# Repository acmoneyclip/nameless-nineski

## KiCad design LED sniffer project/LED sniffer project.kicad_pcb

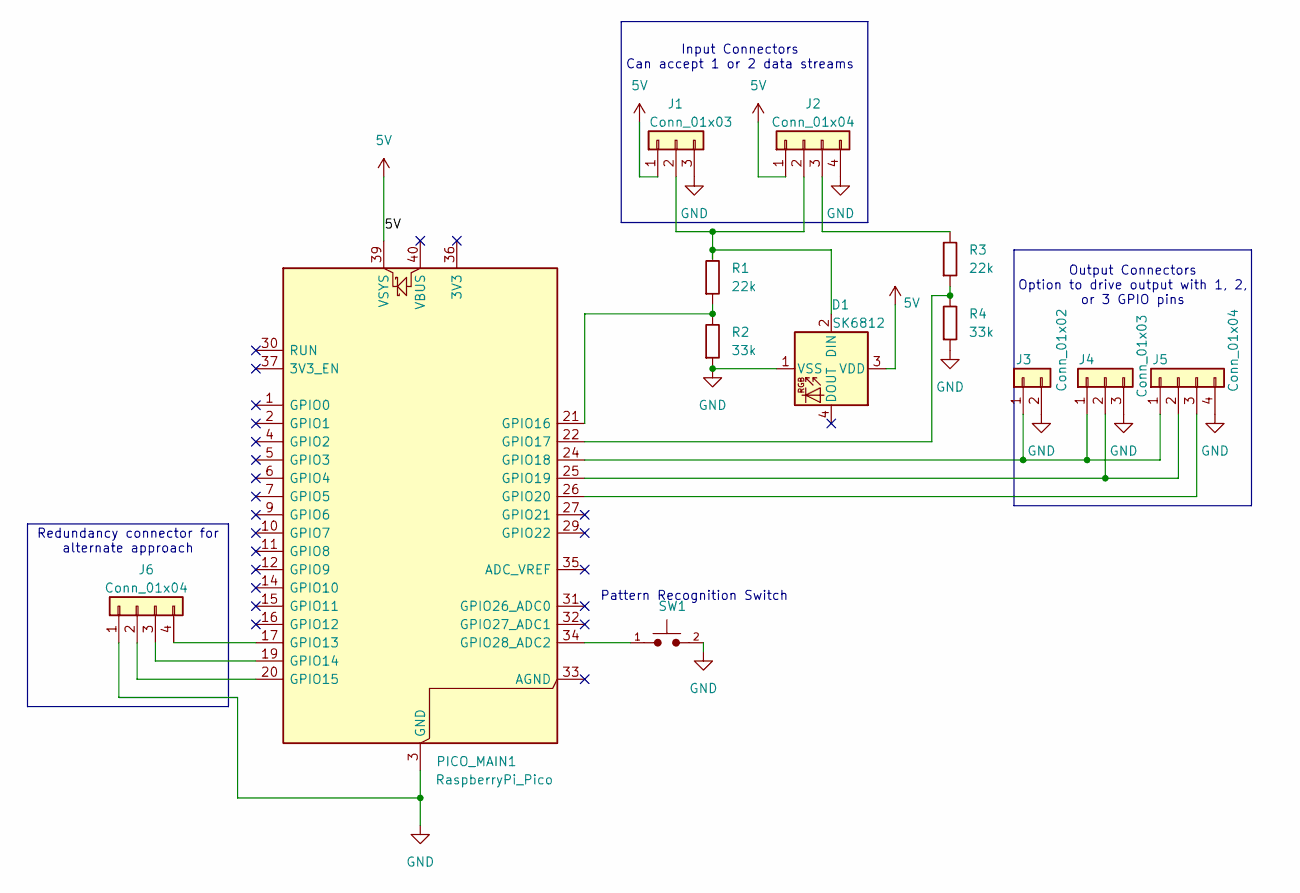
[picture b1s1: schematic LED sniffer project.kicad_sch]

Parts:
D1: SK6812; LED_SK6812_PLCC4_5.0x5.0mm_P3.2mm
J1, J4: Conn_01x03; PinHeader_1x03_P2.54mm_Vertical; Part Number 1-0301FBV0T
J2, J5, J6: Conn_01x04; PinHeader_1x04_P2.54mm_Vertical; Part Number 1-0401FBV0T
J3: Conn_01x02; PinHeader_1x02_P2.54mm_Vertical; Part Number 1-0201FBV0T
PICO_MAIN1: RaspberryPi_Pico; RaspberryPi_Pico_Common_Unspecified
R1, R3: 22k; R_0603_1608Metric
R2, R4: 33k; R_0603_1608Metric
SW1: Push_Button; SW_PUSH_6mm

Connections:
5V: D1.3 (VDD), J1.1, J2.1, PICO_MAIN1.39 (VSYS)
GND: D1.1 (VSS), J1.3, J2.4, J3.2, J4.3, J5.4, J6.1, PICO_MAIN1.3 (GND), PICO_MAIN1.8 (GND), PICO_MAIN1.13 (GND), PICO_MAIN1.18 (GND), PICO_MAIN1.23 (GND), PICO_MAIN1.28 (GND), PICO_MAIN1.38 (GND), R2.1, R4.1, SW1.2
unnamed: D1.2 (DIN), J1.2, J2.2, R1.2
unnamed: J2.3, R3.2
unnamed: J3.1, J4.1, J5.1, PICO_MAIN1.24 (GPIO18)
unnamed: J4.2, J5.2, PICO_MAIN1.25 (GPIO19)
unnamed: J5.3, PICO_MAIN1.26 (GPIO20)
unnamed: J6.2, PICO_MAIN1.20 (GPIO15)
unnamed: J6.3, PICO_MAIN1.19 (GPIO14)
unnamed: J6.4, PICO_MAIN1.17 (GPIO13)
unnamed: PICO_MAIN1.21 (GPIO16), R1.1, R2.2
unnamed: PICO_MAIN1.22 (GPIO17), R3.1, R4.2
unnamed: PICO_MAIN1.34 (GPIO28_ADC2), SW1.1

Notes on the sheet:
Output Connectors Option to drive output with 1, 2, or 3 GPIO pins
Pattern Recognition Switch
Input Connectors Can accept 1 or 2 data streams
Redundancy connector for alternate approach

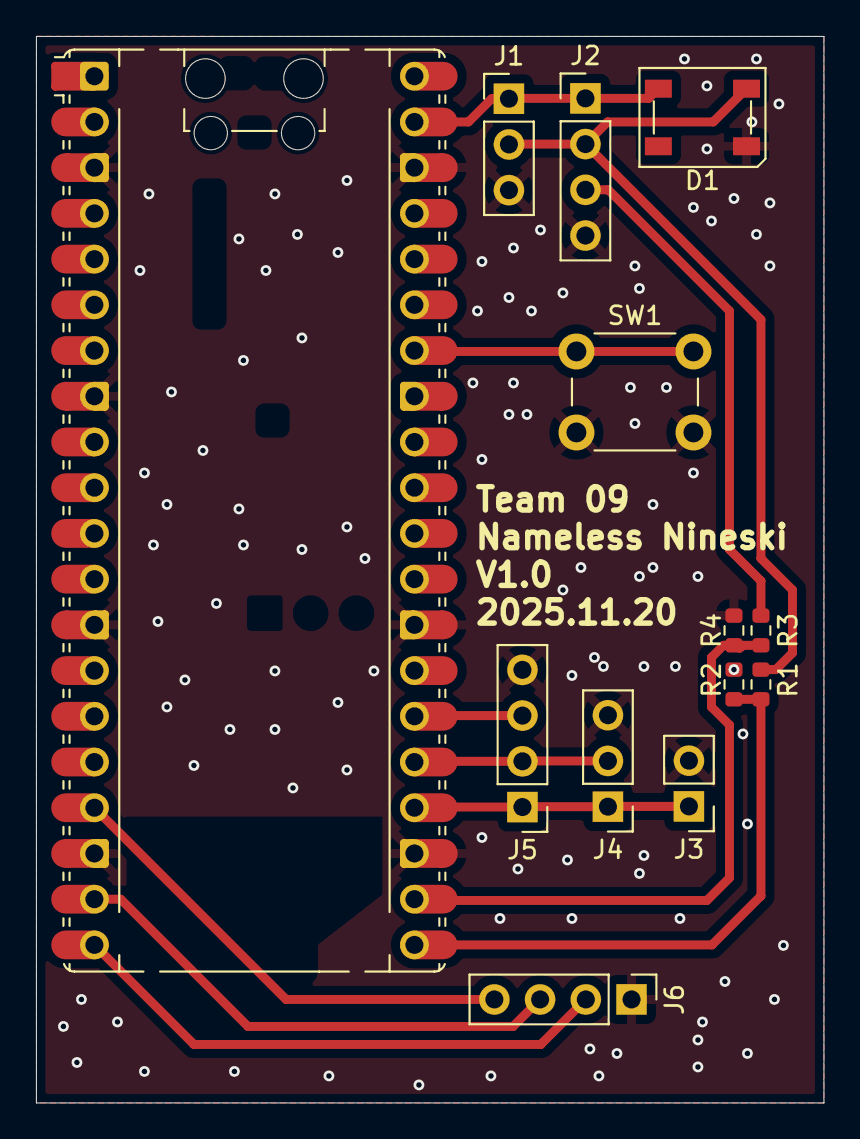
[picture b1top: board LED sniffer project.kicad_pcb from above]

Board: 2 copper layers, 43.8 x 59.2 mm, 13 parts (0 on the bottom side), 13 nets.

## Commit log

2025-10-27 Starting push for our 411 project
2025-11-05 Updated Schematic to Revision 2
    This was designed for building the breadboard under my understanding of the demonstration set up requirements communicated at our team meeting on 11/4/2025
2025-11-05 Added firmware for LED sniffer project
    This commit adds MicroPython firmware for both Raspberry Pi Pico boards used in the LED Sniffer circuit (Revision 2 schematic).
    - pico_gen_main.py: Generates a periodic digital signal on GPIO16 (Din_Gen) to simulate the LED data trigger.
    - pico_sound_main.py: Reads the trigger input, activates the speaker via 2N3904 transistor, and can later be expanded for LED response logic.
    Note: The LED_RGB in the schematic is treated as a digital (single-wire) data LED, not a 3-channel analog RGB LED.
2025-11-06 HW6 updated schematic (revision 2), initial layout, and 3D render
2025-11-10 Bill of Material Export from KiCad LED Sniffer Schematic (Rev 2)
2025-11-10 Update with current breadboard
2025-11-11 aaron's PCB file for CAD rough draft (contains 2 raspberry pi)
    I was thinking at some point that the jumper is not needed since imagine we could be connecting the raspberry pi with usb power....
2025-11-12 rough draft of schematic
2025-11-13 Bill of Materials
    Team 09_BOM
2025-11-18 Updated with a slightly less rough draft
2025-11-18 RGB sniffer prototype files
2025-11-18 Updated CAD
2025-11-19 Create Docs
2025-11-19 Slight update
2025-11-19 Even more updated
2025-11-20 Possible submission
2025-11-20 Get ready for production
2025-11-20 Final Cad
2025-11-20 With PDFs
2025-12-03 added sniffer test plan documents
    test plan and example test case
2025-12-04 Updated Example Test Case
    Updated to explicitly identify this test case as hypothetical. An actual test can be performed when we have an MVP to test.
2025-12-04 Din Generator and Sniffer Code
    Gen: drives a NeoPixel ring on GP2, cycling R/G/B/off.
    Sniff: samples DIN on GP27, learns a target color on button press, and prints MATCH whenever the incoming NeoPixel data is close to the learned color.
2025-12-04 README file for Din_Gen_ac1 and Din_sniff_ac1
2025-12-04 Update README_Din_Sniff_ac1
    added detail that code current only supports start and stopping through Thonny
2025-12-10 Test your GPIO pin to maker it's not blown
    If you're not getting a Din reading, this is a sanity check that will at least tell you if your pin is noticing more than all zeroes. Maybe it can makes sense of Din but it can still tell you it's al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
2025-12-12 run this before using Din_Sniff_ac1
    for some reason sniff code doesn't read any 1's unless this dummy test is run first.
